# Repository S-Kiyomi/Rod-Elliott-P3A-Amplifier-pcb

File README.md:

# Rod Elliott P3A Amplifier (myself made DIY-PCB)

## Schematic

### Cara Kerja Rangkaian

seperti amplifier class ab pada umumnya. dokumentasi lengkap [disini](https://sound-au.com/project3a.htm)

### PENTING!!

schematic sepenuhnya milik Rod Elliott. hanya digunakan untuk tujuan pembelajaran. DILARANG KERAS MENJADIKAN PROJECT INI UNTUK KOMERSIAL sesuai hak cipta yang tertulis 

### Copyright Notice
"This article, including but not limited to all text and diagrams, is the intellectual property of Rod Elliott, and is © 2000-2009.  Reproduction or re-publication by any means whatsoever, whether electronic, mechanical or electro- mechanical, is strictly prohibited under International Copyright laws.  The author (Rod Elliott) grants the reader the right to use this information for personal use only, and further allows that one (1) copy may be made for reference while constructing the project.  Commercial use is prohibited without express written authorisation from Rod Elliott"

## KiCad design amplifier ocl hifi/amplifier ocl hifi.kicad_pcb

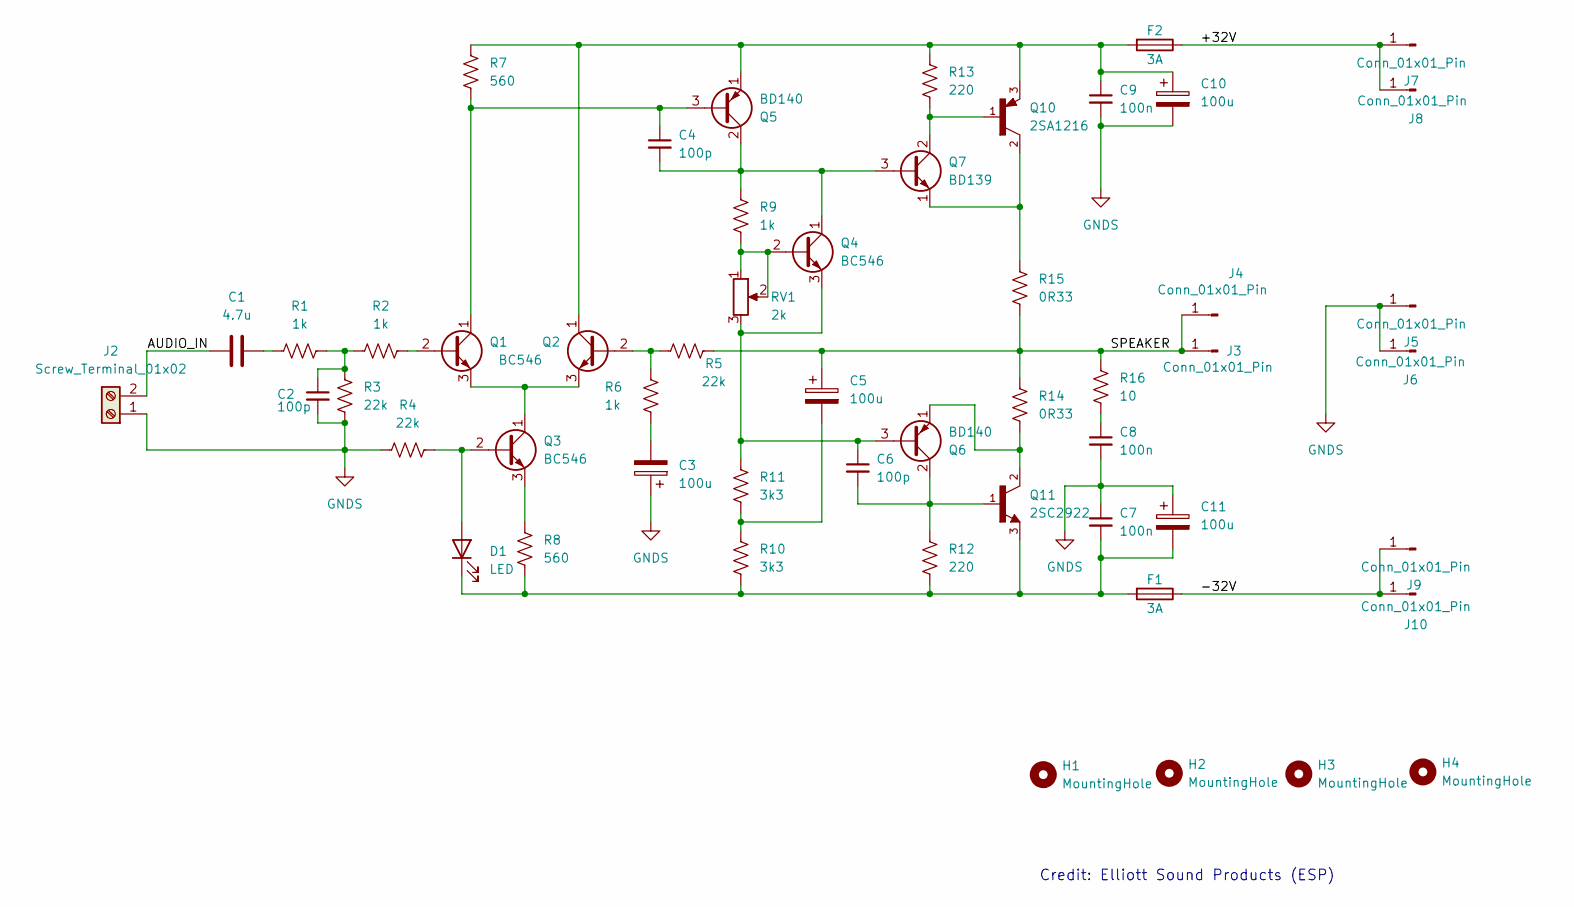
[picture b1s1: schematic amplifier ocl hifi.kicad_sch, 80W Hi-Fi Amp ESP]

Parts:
C1: 4.7u; C_Axial_L22.0mm_D10.5mm_P27.50mm_Horizontal
C2, C4, C6: 100p; C_Rect_L7.2mm_W3.5mm_P5.00mm_FKS2_FKP2_MKS2_MKP2
C3, C5, C10, C11: 100u; CP_Radial_D8.0mm_P3.80mm
C7, C8, C9: 100n; C_Rect_L7.2mm_W3.5mm_P5.00mm_FKS2_FKP2_MKS2_MKP2
D1: LED; LED_D3.0mm
F1, F2: 3A; Fuseholder_Clip-5x20mm_Eaton_1A5601-01_Inline_P20.80x6.76mm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
H1, H2, H3, H4: MountingHole; MountingHole_2.1mm
J2: Screw_Terminal_01x02; Altech_AK100_1x02_P5.00mm
J3, J4, J5, J6, J7, J8, J9, J10: Conn_01x01_Pin; SolderWire-0.5sqmm_1x01_D0.9mm_OD2.3mm
Q1, Q2, Q3, Q4: BC546; TO-92_Wide
Q5, Q6: BD140; TO-126-3_Vertical
Q7: BD139; TO-126-3_Vertical
Q10: 2SA1216; TRANS_2SA1216; PARTREV N/A
Q11: 2SC2922; TRANS_2SA1216
R1, R2, R6, R9: 1k; R_Axial_DIN0207_L6.3mm_D2.5mm_P10.16mm_Horizontal
R3, R4, R5: 22k; R_Axial_DIN0207_L6.3mm_D2.5mm_P10.16mm_Horizontal
R7, R8: 560; R_Axial_DIN0207_L6.3mm_D2.5mm_P10.16mm_Horizontal
R10, R11: 3k3; R_Axial_DIN0309_L9.0mm_D3.2mm_P12.70mm_Horizontal
R12, R13: 220; R_Axial_DIN0207_L6.3mm_D2.5mm_P10.16mm_Horizontal
R14, R15: 0R33; R_Axial_Power_L20.0mm_W6.4mm_P22.40mm
R16: 10; R_Axial_DIN0309_L9.0mm_D3.2mm_P12.70mm_Horizontal
RV1: 2k; Potentiometer_Bourns_3296W_Vertical

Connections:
/+32V: F2.1, J7.1 (Pin_1_1), J8.1 (Pin_1_1)
/-32V: F1.1, J9.1 (Pin_1_1), J10.1 (Pin_1_1)
/AUDIO_IN: C1.1, J2.2
/SPEAKER: C5.1, J3.1 (Pin_1_1), J4.1 (Pin_1_1), R5.1, R14.1, R15.2, R16.1
GNDS: C2.2, C3.1, C7.1, C8.2, C9.2, C10.2, C11.1, J2.1, J5.1 (Pin_1_1), J6.1 (Pin_1_1), R3.1, R4.2
unnamed: C1.2, R1.1
unnamed: C2.1, R1.2, R2.1, R3.2
unnamed: C3.2, R6.2
unnamed: C5.2, R10.1, R11.2
unnamed: C8.1, R16.2
unnamed: D1.2 (A), Q3.2 (B), R4.1
unnamed 11: C7.2, C11.2, D1.1 (K), F1.2, Q11.3, R8.2, R10.2, R12.2; also elsewhere on the board
unnamed: Q1.2 (B), R2.2
unnamed: C4.1, Q1.1 (C), Q5.3 (B), R7.2
unnamed: Q1.3 (E), Q2.3 (E), Q3.1 (C)
unnamed: Q2.2 (B), R5.2, R6.1
unnamed 16: C9.1, C10.1, F2.2, Q2.1 (C), Q5.1 (E), Q10.3, R7.1, R13.1; also elsewhere on the board
unnamed: Q3.3 (E), R8.1
unnamed: Q4.2 (B), R9.2, RV1.1, RV1.2
unnamed 19: C4.2, Q4.1 (C), Q5.2 (C), Q7.3 (B), R9.1; also elsewhere on the board
unnamed: C6.1, Q4.3 (E), Q6.3 (B), R11.1, RV1.3
unnamed 21: C6.2, Q6.2 (C), Q11.1, R12.1; also elsewhere on the board
unnamed 22: Q6.1 (E), Q11.2, R14.2; also elsewhere on the board
unnamed 23: Q7.2 (C), Q10.1, R13.2; also elsewhere on the board
unnamed 24: Q7.1 (E), Q10.2, R15.1; also elsewhere on the board

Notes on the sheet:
Credit: Elliott Sound Products (ESP)

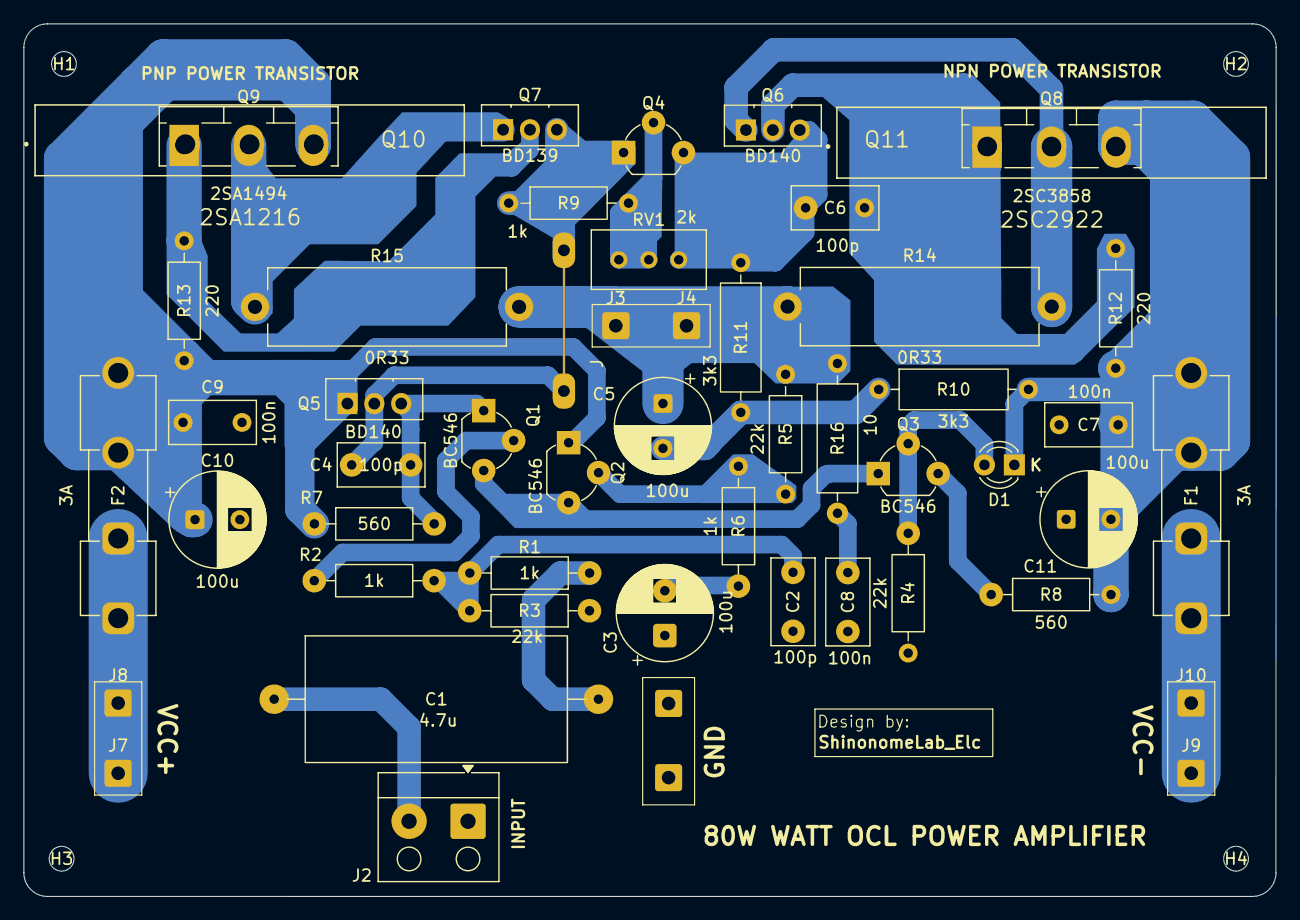
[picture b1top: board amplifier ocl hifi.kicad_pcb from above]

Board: 2 copper layers, 106.2 x 74.0 mm, 56 parts (0 on the bottom side), 25 nets.

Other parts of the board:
J: Jumper-Wire_12mm_Blue
Q8: 2SC3858; TO-218-3_Vertical
Q9: 2SA1494; TO-218-3_Vertical

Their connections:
unnamed 11: Q8.3 (E); also elsewhere on the board
unnamed 16: Q9.3 (E); also elsewhere on the board
unnamed 19: J.1, J.2; also elsewhere on the board
unnamed 21: Q8.1 (B); also elsewhere on the board
unnamed 22: Q8.2 (C); also elsewhere on the board
unnamed 23: Q9.1 (B); also elsewhere on the board
unnamed 24: Q9.2 (C); also elsewhere on the board
